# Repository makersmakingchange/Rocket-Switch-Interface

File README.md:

# Rocket Switch Interface
The Rocket Switch Interface is a switch interface device which enables users to operate their computer or smartphone devices using assistive switches. The Rocket Switch Interface supports up to two 3.5 mm assistive switches as input.

## More info at
- [Makers Making Change Project Page](https://makersmakingchange.com/project/rocket-switch-interface/)

## Usage
Both switches can be used as inputs when short pressed, Switch 1 can be used to change the operation mode when it's pressed and hold for 4 seconds. The device can operate in several modes:

 - Switch Mac Mode: This mode can be used along switch control software available for Windows, Android, iOS, and Mac Operating Systems. Switch 1 outputs the Space key and switch 2 outputs the Enter key.

 - Switch Mode: This mode can be used along switch control software available for Windows, Android, and iOS Operating Systems. Switch 1 outputs the 1 key and switch 2 outputs the 2 key.

 - Mouse Mode: This mode can be used to simulate a mouse button click. Switch 1 performs left mouse click and switch 2 performs right mouse click.

 - Settings Mode: The settings mode allows the user to adjust the reaction time between switch presses. There are 10 levels in total and the default reaction level is set to 9. The minimum reaction time is 50ms ( Level 10 ) and maximum reaction time is 500ms ( Level 1 ). Switch 1 decrements the reaction level by 1 level and switch 2 increments the reaction level by 1 level as well.

## How to Obtain a Rocket Switch Interface

### 1. Do it Yourself (DIY) or Do it Together (DIT)

This is an open-source assistive technology, so anyone is free to build it. All of the files and instructions required to build the device are contained within this repository. Refer to the Maker Checklist below.

### 2. Request a build of this device

If you would like to obtain this device, you may submit a build request through the [MMC Library Page](https://makersmakingchange.com/project/rocket-switch-interface/). The requestor is responsible for the cost of materials and any shipping.

### 3. How to build this device for someone else

If you have the skills and equipment to build this device, and would like to donate your time to create the switch for someone who needs it, visit the [MMC Maker Wanted](https://makersmakingchange.com/maker-wanted/) section.

## Getting Started

### 1. Read the Makers Checklist

The Makers Checklist provides an overview of the steps required to build this device.

### 2. Order the Off-The-Shelf Components

The [Bill of Materials](/Documentation/Rocket_Switch_Interface_BOM.xlsx) lists all of the parts and components required to build the Rocket Switch Interface.

### 3. Print the 3D Printable components

All of the files and individual print files can be in the [/Build_Files/3D_Printing_Files](/Build_Files/3D_Printing/) folder.

### 4. Assemble the Device

Reference the [Assembly Guide](/Documentation/Rocket_Switch_Interface_Assembly_Guide.pdf) for the tools and steps required to build each portion.

## Files
### Documentation
| Document             | Version | Link |
|----------------------|---------|------|
| Design Rationale     | 1.1     | [Rocket Switch Interface Design_Rationale](/Documentation/Rocket_Switch_Interface_Design_Rationale.pdf)     |
| Maker Checklist      | 1.1     | [Rocket Switch Interface Link_Maker_Checklist](/Documentation/Rocket_Switch_Interface_Maker_Checklist.pdf)     |
| Bill of Materials    | 1.1     | [Rocket Switch Interface Link_Bill_of_Materials](/Documentation/Rocket_Switch_Interface_BOM.xlsx)     |
| 3D Printing Guide    | 1.1     | [Rocket Switch Interface Link_3D_Printing_Guide](/Documentation/Rocket_Switch_Interface_3D_Printing_Guide.pdf)     |
| Assembly Guide       | 1.1     | [Rocket Switch Interface Link_Assembly_Guide](/Documentation/Rocket_Switch_Interface_Assembly_Guide.pdf)     |
| User Guide           | 1.1     | [Rocket Switch Interface Link_User_Guide](/Documentation/Rocket_Switch_Interface_User_Guide.pdf)    |
| Changelog            | 1.1     | [Rocket Switch Interface Link_Changelog](/Documentation/Rocket_Switch_Interface_Changelog.pdf)     |

### Design Files
 - [CAD Files](/Design_Files)

### Build Files
 - [3D Printing Files](/Build_Files/3D_Printing_Files)

## Attribution
Designers:
 - Milad Hajihassan, Makers Making Change

Contributors:
 - Derrick Andrews, Makers Making Change

## License
Everything needed or used to design, make, test, or prepare the Rocket Switch Interface Link is licensed under the CERN 2.0 Weakly Reciprocal license <https://ohwr.org/project/cernohl/wikis/Documents/CERN-OHL-version-2> (CERN-OHL-W) . 

Accompanying material such as instruction manuals, videos, and other copyrightable works that are useful but not necessary to design, make, test, or prepare the Rocket Switch Interface are published under a Creative Commons Attribution-ShareAlike 4.0 license https://creativecommons.org/licenses/by-sa/4.0/ (CC BY-SA 4.0).

----

<!-- ABOUT MMC START -->
## About Makers Making Change

Makers Making Change is a program of [Neil Squire](https://www.neilsquire.ca/), a Canadian non-profit that uses technology, knowledge, and passion to empower people with disabilities.

Makers Making Change leverages the capacity of community based Makers, Disability Professionals and Volunteers to develop and deliver affordable Open Source Assistive Technologies.

 - Website: [www.MakersMakingChange.com](https://www.makersmakingchange.com/)
 - GitHub: [makersmakingchange](https://github.com/makersmakingchange)
 - Bluesky: [@makersmakingchange.bsky.social](https://bsky.app/profile/makersmakingchange.bsky.social)
 - Instagram: [@makersmakingchange](https://www.instagram.com/makersmakingchange)
 - Facebook: [makersmakechange](https://www.facebook.com/makersmakechange)
 - LinkedIn: [Neil Squire Society](https://www.linkedin.com/company/neil-squire-society/)
 - Thingiverse: [makersmakingchange](https://www.thingiverse.com/makersmakingchange/about)
 - Printables: [MakersMakingChange](https://www.printables.com/@MakersMakingChange)

### Contact Us
For technical questions, to get involved, or to share your experience we encourage you to [visit our website](https://www.makersmakingchange.com/) or [contact us](https://www.makersmakingchange.com/s/contact).
<!-- ABOUT MMC END -->

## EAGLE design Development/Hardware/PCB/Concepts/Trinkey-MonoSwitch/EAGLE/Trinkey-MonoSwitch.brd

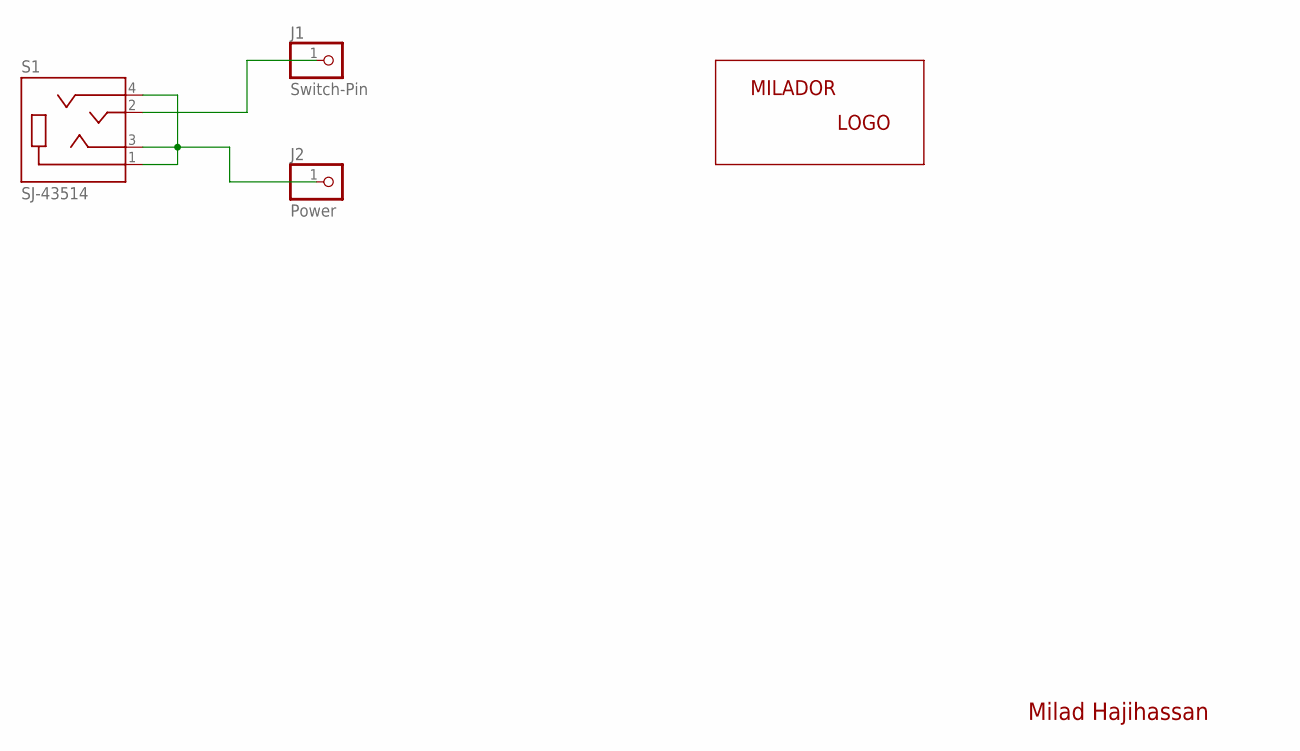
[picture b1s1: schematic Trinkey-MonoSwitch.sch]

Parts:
J1: Switch-Pin; CASTELLATED_PIN-1X01
J2: Power; CASTELLATED_PIN-1X01
LABEL-LOGO: MILADOR-LOGO-SM; MILADOR_LOGO2
S1: SJ-43514; CUI_SJ-43514

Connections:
unnamed: J1.1, S1.2 (TIP)
unnamed: J2.1, S1.1 (SLEEVE), S1.3 (RING1), S1.4 (RING2)

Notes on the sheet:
Milad Hajihassan

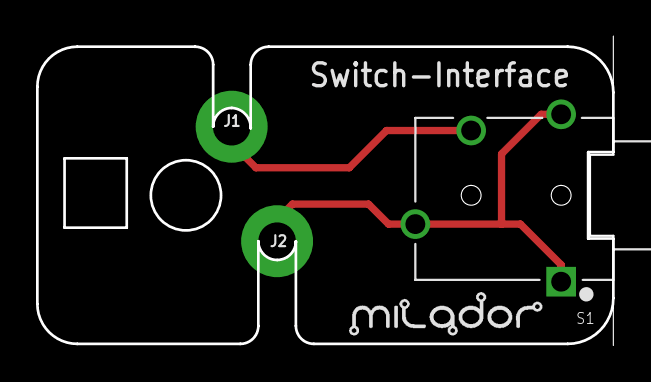
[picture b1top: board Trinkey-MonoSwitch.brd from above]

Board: 2 copper layers, 32.0 x 17.1 mm, 4 parts (0 on the bottom side), 2 nets.

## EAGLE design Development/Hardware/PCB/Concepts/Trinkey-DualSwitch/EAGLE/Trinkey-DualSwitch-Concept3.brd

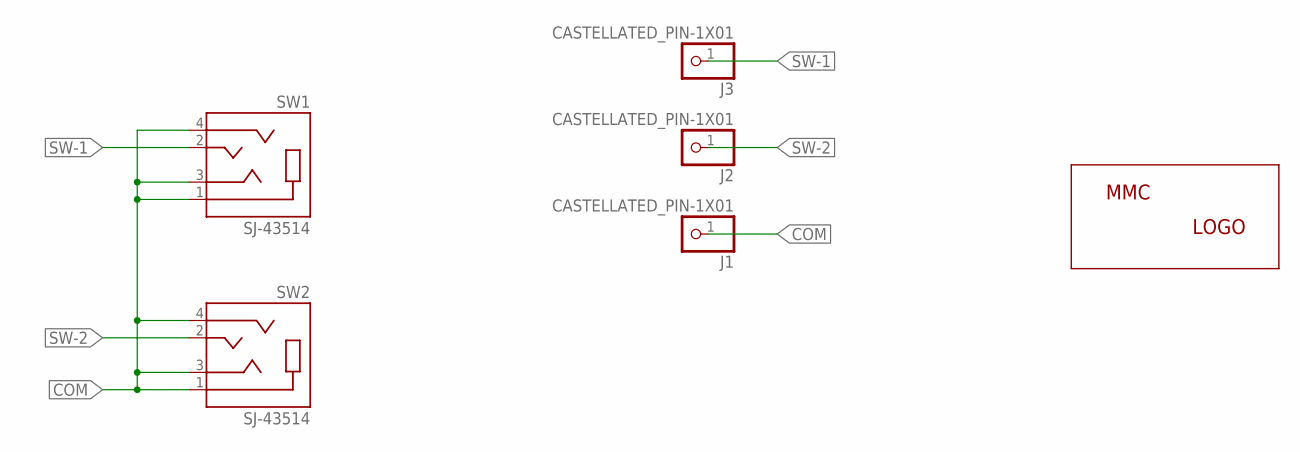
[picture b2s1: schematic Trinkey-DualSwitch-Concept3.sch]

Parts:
J1, J2, J3: CASTELLATED_PIN-1X01
LABEL_LOGO: MMC_LOGO-XSM; MMC_X-SMALL_LOGO
SW1, SW2: SJ-43514; CUI_SJ-43514

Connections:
COM: J1.1, SW1.1 (SLEEVE), SW1.3 (RING1), SW1.4 (RING2), SW2.1 (SLEEVE), SW2.3 (RING1), SW2.4 (RING2)
SW-1: J3.1, SW1.2 (TIP)
SW-2: J2.1, SW2.2 (TIP)

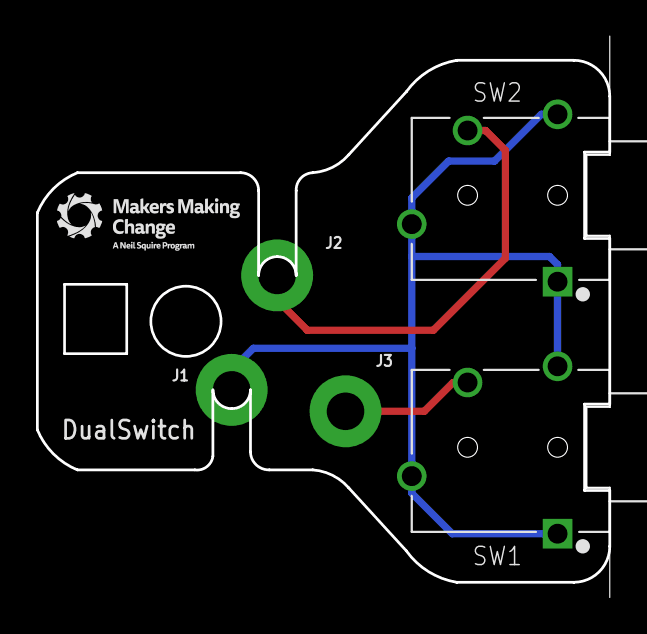
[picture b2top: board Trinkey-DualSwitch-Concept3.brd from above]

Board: 2 copper layers, 31.8 x 31.0 mm, 6 parts (0 on the bottom side), 3 nets.

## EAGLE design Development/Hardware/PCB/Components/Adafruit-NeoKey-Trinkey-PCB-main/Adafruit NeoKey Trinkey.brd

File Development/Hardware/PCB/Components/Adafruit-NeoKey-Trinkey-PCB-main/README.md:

## Adafruit NeoKey Trinkey PCB

<a href="http://www.adafruit.com/products/5020"><br/>
Click here to purchase one from the Adafruit shop</a>

PCB files for the Adafruit NeoKey Trinkey. 

Format is EagleCAD schematic and board layout
* https://www.adafruit.com/product/5020

### Description

It's half USB Key, half Adafruit Trinket, half mechanical keeb...it's NeoKey Trinkey, the circuit board with a Trinket M0 heart, a NeoPixel glow, and a Cherry MX-compatible. We were inspired by single-key macro pads we've seen. So we thought, hey what if we made something like that that plugs right into your computer's USB port, with a fully programmable color NeoPixel? And this is what we came up with!

The PCB is designed to slip into any USB A port on a computer or laptop. There's an ATSAMD21 microcontroller on board with just enough circuitry to keep it happy. One pin of the microcontroller connects to a Cherry MX-compatible switch. Another connects to a NeoPixel LED. The third pin can be used as a capacitive touch input. A reset button lets you enter bootloader mode if necessary. That's it!

The SAMD21 can run CircuitPython or Arduino very nicely - with existing NeoPixel and our FreeTouch libraries for the capacitive touch input. Over the USB connection you can have serial, MIDI or HID connectivity. The NeoKey Trinkey is perfect for simple projects that can use a few user inputs and colorful output. Maybe you'll set it up as a macro-controller, or a password-enterer, or an Escape key for your MacBook.

Please note this board DOES NOT come with a key soldered in - we expect folks to pick their favorite MX-compatible key switch and key cap! Two solder points and you're done.

We think it's just an adorable little board, small and durable and inexpensive enough that it could be a first microcontroller board, or inspiration for advanced developers to make something simple and fun.

* ATSAMD21E18 32-bit Cortex M0+ - 48 MHz 32 bit processor with 256KB Flash and 32 KB RAM
* Native USB supported by every OS - can be used in Arduino or CircuitPython as USB serial console, MIDI, Keyboard/Mouse HID, even a little disk drive for storing Python scripts.
* Can be used with Arduino IDE or CircuitPython
* Single reverse-mount RGB NeoPixel LED
* One Capacitive Touch pad
* Cherry-MX compatible footprint can be used by nearly any mechanical switch. Note we only have a center-nub hole. If your switch has two mini side-nubs they need to be clipped off.
* Reset switch for starting your project code over or entering bootloader mode
* Cute & keychain-friendly!

### License

Adafruit invests time and resources providing this open source design, please support Adafruit and open-source hardware by purchasing products from [Adafruit](https://www.adafruit.com)!

Designed by Limor Fried/Ladyada for Adafruit Industries.

Creative Commons Attribution/Share-Alike, all text above must be included in any redistribution. 
See license.txt for additional details.

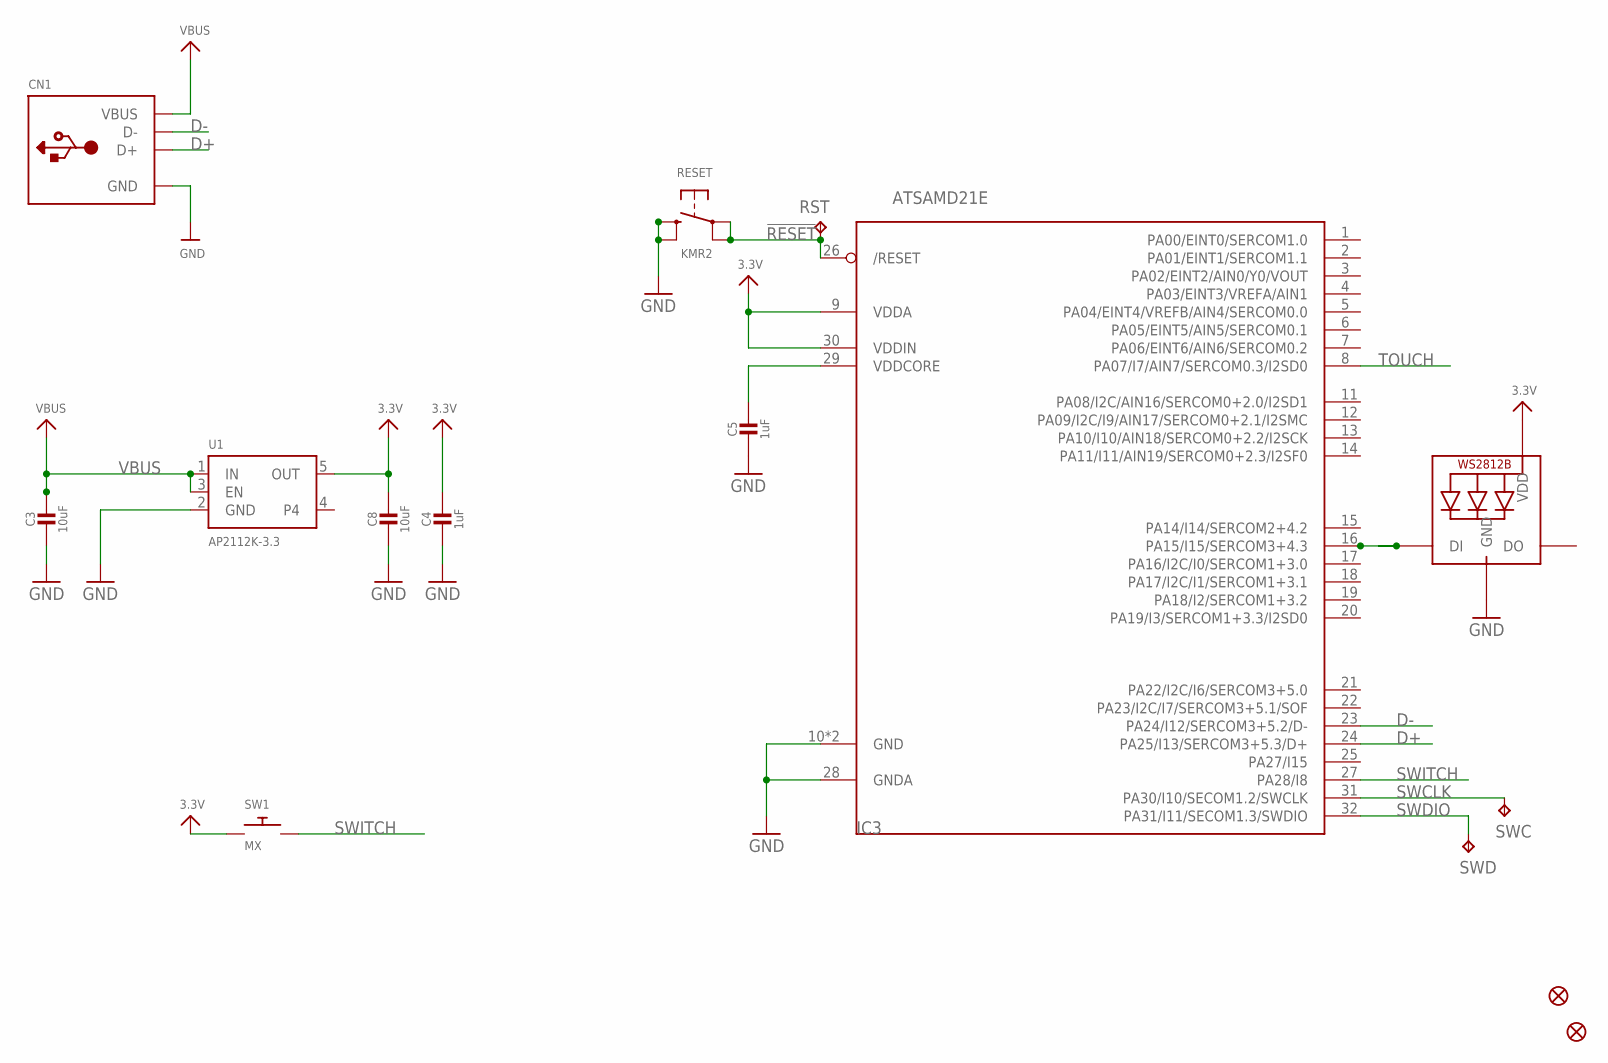
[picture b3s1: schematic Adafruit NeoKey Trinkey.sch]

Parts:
C3, C8: 10uF; 0805-NO
C4, C5: 1uF; 0603-NO
CN1: USB_TYPEAPCB; USBA_PCB
FID1, FID2: FIDUCIAL_1MM
IC3: ATSAMD21E; QFN32_5MM
LED1: WS2812B_SK6812E; NEO3535_REVERSE
RESET: KMR2; BTN_KMR2_4.6X2.8
RST: RST; TP16R
SW1: MX; KAILH_BOX_MX_NOSTABILIZERS
SWC: SWC; TP15R
SWD: SWD; TP15R
U1: AP2112K-3.3; SOT23-5

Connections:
3.3V: C4.1, C8.1, IC3.9 (VDDA), IC3.30 (VDDIN), LED1.1-VDD (VDD), SW1.1, U1.5 (OUT)
!RESET: IC3.26 (/RESET), RESET.A, RESET.A' (P1), RST.TP
D+: CN1.USB_PLUS (D+), IC3.24 (PA25/I13/SERCOM3+5.3/D+)
D-: CN1.USB_NEG (D-), IC3.23 (PA24/I12/SERCOM3+5.2/D-)
GND: C3.2, C4.2, C5.2, C8.2, CN1.GND, IC3.10 (GND), IC3.28 (GNDA), IC3.33 (GND), LED1.3-GND (GND), RESET.B (S), RESET.B' (S1), U1.2 (GND)
unnamed: IC3.16 (PA15/I15/SERCOM3+4.3), LED1.4-DIN (DI)
SWCLK: IC3.31 (PA30/I10/SECOM1.2/SWCLK), SWC.TP
SWDIO: IC3.32 (PA31/I11/SECOM1.3/SWDIO), SWD.TP
SWITCH: IC3.27 (PA28/I8), SW1.2
TOUCH: IC3.8 (PA07/I7/AIN7/SERCOM0.3/I2SD0)
VBUS: C3.1, CN1.VCC (VBUS), U1.1 (IN), U1.3 (EN)
VDDCORE1: C5.1, IC3.29 (VDDCORE)

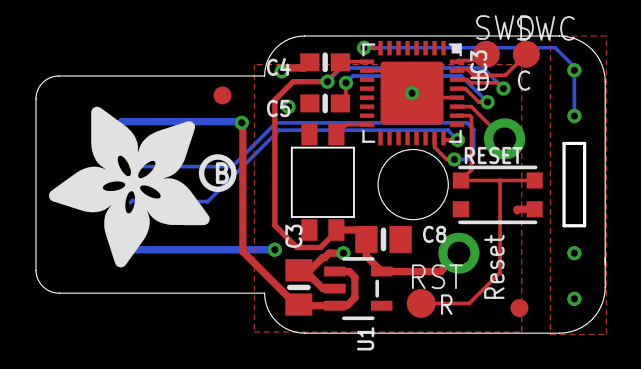
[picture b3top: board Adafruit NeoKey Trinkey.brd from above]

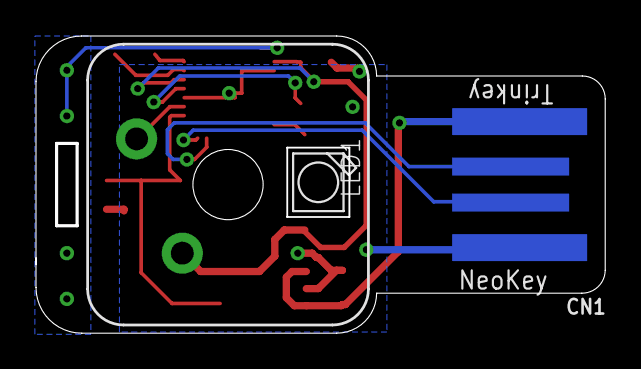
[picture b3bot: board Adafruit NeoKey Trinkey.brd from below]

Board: 2 copper layers, 31.4 x 16.3 mm, 17 parts (3 on the bottom side), 11 nets.

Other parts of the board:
U$6: ADAFRUIT_9MM
U$8: PCBFEAT-REV-040

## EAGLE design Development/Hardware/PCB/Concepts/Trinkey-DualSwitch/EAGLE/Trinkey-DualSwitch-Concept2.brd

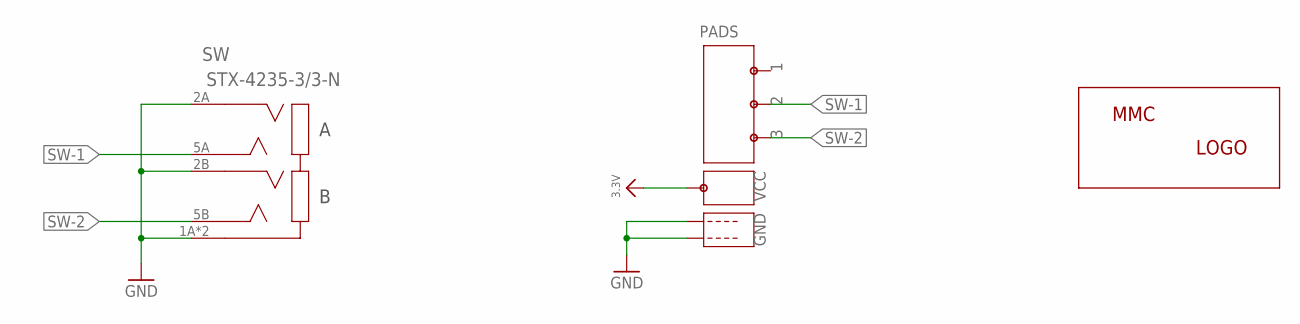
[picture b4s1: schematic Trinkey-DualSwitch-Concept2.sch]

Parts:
LABEL_LOGO: MMC_LOGO-XSM; MMC_X-SMALL_LOGO
PADS: CASTELLATED-ROTARY-TRINKEY
SW: STX-4235-3/3-N; STX-4235-3/3

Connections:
3.3V: PADS.P$VCC
GND: PADS.P$GND1, PADS.P$GND2, SW.1A (1AB), SW.1B (1AB), SW.2A, SW.2B
SW-1: PADS.P$S2, SW.5A
SW-2: PADS.P$S3, SW.5B

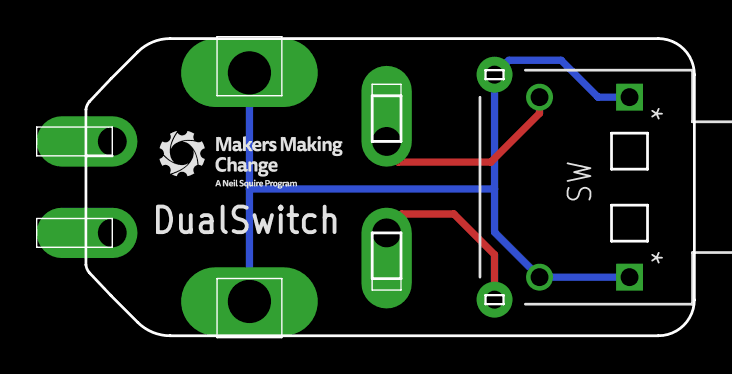
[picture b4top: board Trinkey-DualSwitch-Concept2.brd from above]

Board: 2 copper layers, 36.5 x 16.6 mm, 3 parts (1 on the bottom side), 3 nets.

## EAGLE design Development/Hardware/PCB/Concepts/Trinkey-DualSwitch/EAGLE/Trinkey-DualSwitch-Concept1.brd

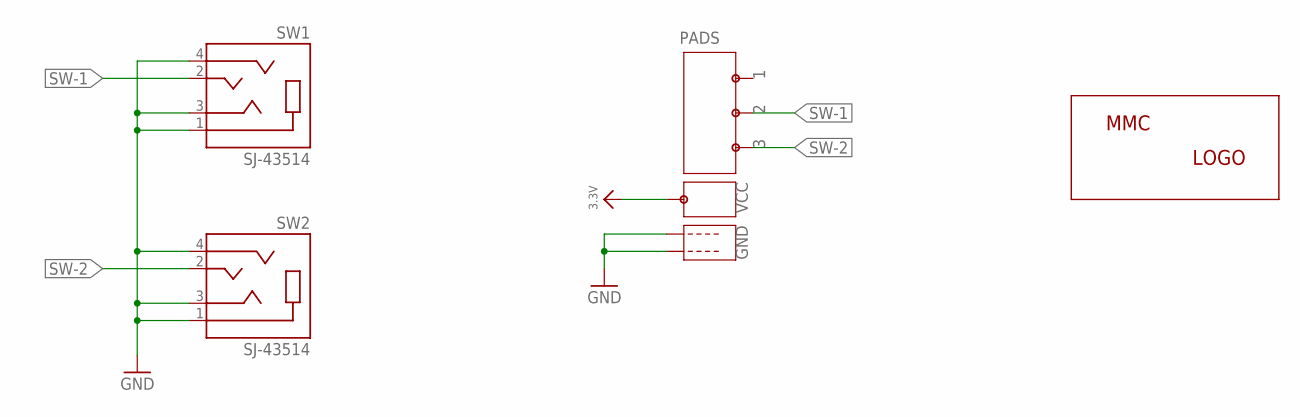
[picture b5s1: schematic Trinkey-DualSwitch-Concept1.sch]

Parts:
LABEL_LOGO: MMC_LOGO-XSM; MMC_X-SMALL_LOGO
PADS: CASTELLATED-ROTARY-TRINKEY
SW1, SW2: SJ-43514; CUI_SJ-43514

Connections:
3.3V: PADS.P$VCC
GND: PADS.P$GND1, PADS.P$GND2, SW1.1 (SLEEVE), SW1.3 (RING1), SW1.4 (RING2), SW2.1 (SLEEVE), SW2.3 (RING1), SW2.4 (RING2)
SW-1: PADS.P$S2, SW1.2 (TIP)
SW-2: PADS.P$S3, SW2.2 (TIP)

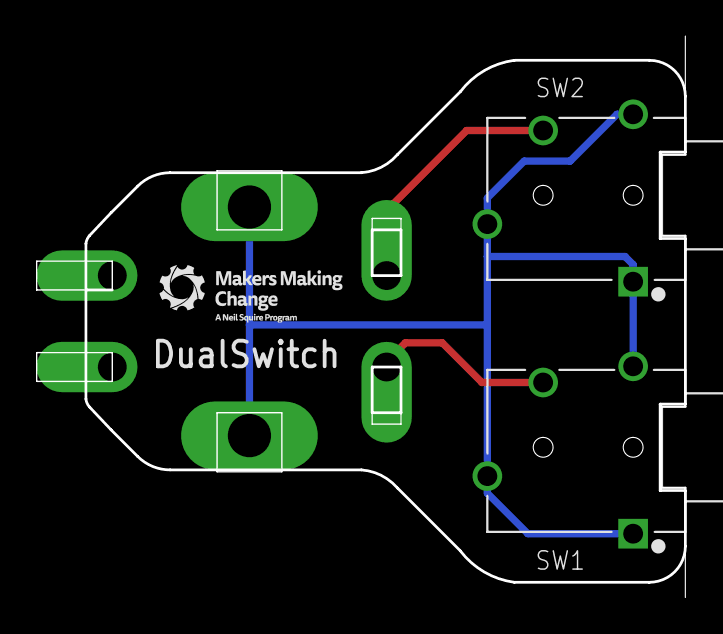
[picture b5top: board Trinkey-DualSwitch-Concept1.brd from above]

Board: 2 copper layers, 36.0 x 31.0 mm, 4 parts (1 on the bottom side), 3 nets.

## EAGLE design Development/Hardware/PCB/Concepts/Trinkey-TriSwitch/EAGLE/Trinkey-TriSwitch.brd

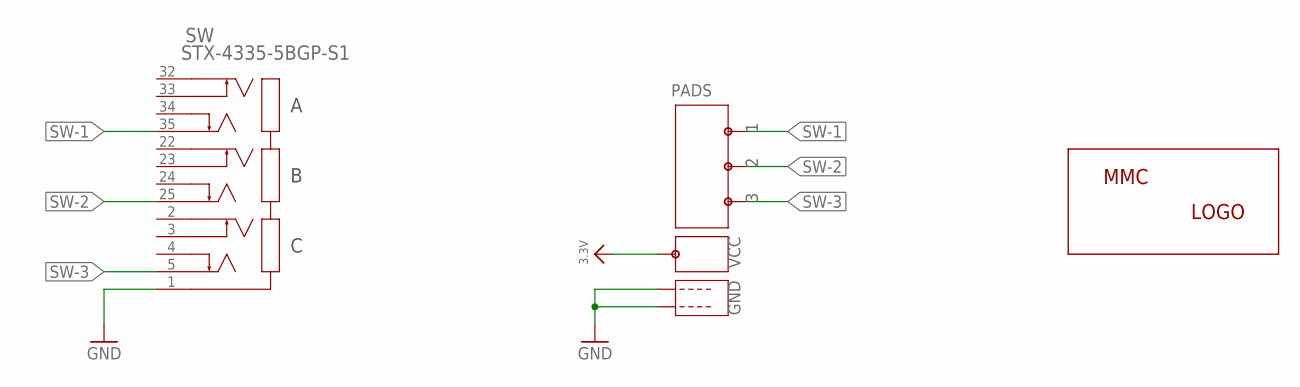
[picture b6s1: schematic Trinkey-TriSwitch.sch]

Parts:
LABEL_LOGO: MMC_LOGO-XSM; MMC_X-SMALL_LOGO
PADS: CASTELLATED-ROTARY-TRINKEY
SW: STX-4335-5BGP-S1; STX-4335-5BGP-S1_KYC

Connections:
3.3V: PADS.P$VCC
GND: PADS.P$GND1, PADS.P$GND2, SW.1
SW-1: PADS.P$S1, SW.35
SW-2: PADS.P$S2, SW.25
SW-3: PADS.P$S3, SW.5

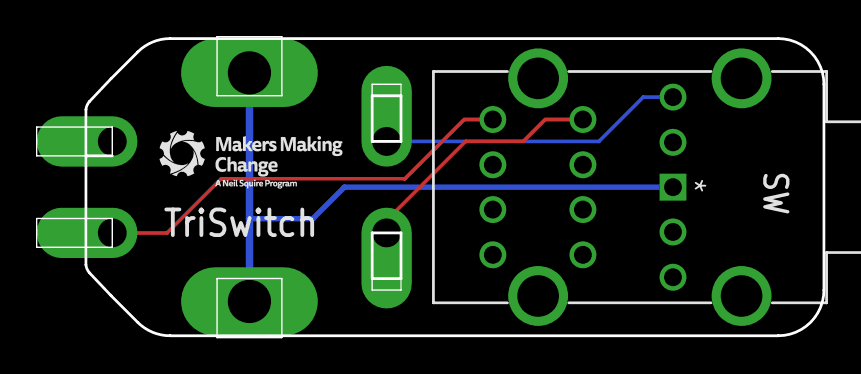
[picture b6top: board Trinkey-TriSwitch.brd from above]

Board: 2 copper layers, 43.7 x 16.6 mm, 3 parts (1 on the bottom side), 4 nets.

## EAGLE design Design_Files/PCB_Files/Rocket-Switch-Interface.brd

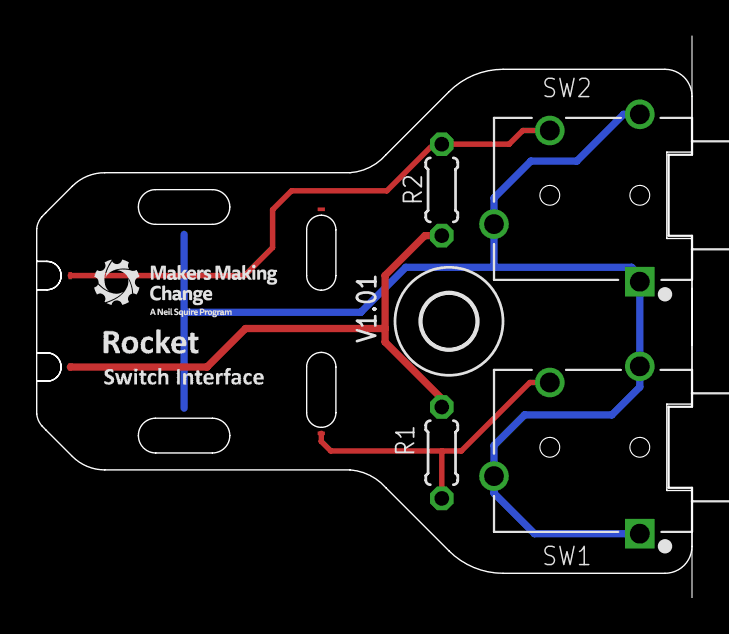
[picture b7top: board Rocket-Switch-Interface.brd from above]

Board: 2 copper layers, 36.4 x 31.1 mm, 9 parts (1 on the bottom side), 4 nets.

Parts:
H1: MOUNT-HOLE-3MM-CLEAR; HOLE-3MM-CLEAR
LABEL_BACKGROUND: MMC_ICON-ROCKET-SW; ICON_ROCKET-SWITCH
LABEL_DEVICE: MMC_LABEL-ROCKET-SW; LABEL-ROCKET-SWITCH
LABEL_LOGO: MMC_LOGO-XSM; MMC_X-SMALL_LOGO
PADS: PADS-ROTARY-TRINKEY-3
R1, R2: 4.7K; RESISTOR_0204/5
SW1, SW2: SJ-43514; CUI_SJ-43514

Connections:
3.3V: PADS.P$VCC, R1.2, R2.2
GND: PADS.P$GND1, PADS.P$GND2, SW1.1, SW1.3, SW1.4, SW2.1, SW2.3, SW2.4
SW-1: PADS.P$ROT2, R1.1, SW1.2
SW-2: PADS.P$SW, R2.1, SW2.2

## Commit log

2022-10-29 Added version 1.0 build, design, and documentation files
2022-10-29 Updated readme links
2022-10-31 Updated Design Rationale: Additional information for improvement
2022-11-16 Updated User Manual and Design Rationale
2022-11-21 Pre-publishing Update
2022-11-23 Updated User Guide
2022-11-23 Fixed software bug : Mode change timer
2023-04-09 Add a simple HID Keyboard CP version
2023-04-09 removed modifier key
2023-04-09 init commit
2023-06-01 Updated to version 1.1
2024-02-26 Added codes for iOS to test
2024-02-26 Update version number and standard naming
2024-02-26 Clean up files
2024-03-01 Squashed commit of the following:
    commit 67a842c9c3a18c6eda38f0db005fe26a0a883580
    Author: jversloot <50920198+jversloot@users.noreply.github.com>
    Date: Fri Mar 1 13:27:49 2024 -0400
    Update for Mac compatibility
    commit ae126e2ec981ad1246a28c21ee91814fd7234fd7
    Author: jversloot <50920198+jversloot@users.noreply.github.com>
2024-03-04 Add license files
2024-03-04 Move Circuit Python files
2025-04-10 Add Update About MMC GitHub Action
2025-04-12 Update About MMC Section
2025-05-08 Move CAD Files
2025-05-08 Add Light Pipe CAD files
2025-06-06 Added guide for using with Apple mobile devices
2025-06-06 Updated Readme with last date
    Added date of last update to readme.

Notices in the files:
parts and their libraries:
microbuilder: This work is placed in the public domain, and may be freely used for commercial and non-commercial work with the following conditions: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
COPYRIGHT: Copyright (C) 2022 Ultra Librarian. All rights reserved.
